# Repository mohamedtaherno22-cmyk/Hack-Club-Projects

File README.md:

Super Starbie
Super Starbie is a small, interactive desktop pet. Its a Starbie but with customized to my liking.

## What Can Super Starbie Do?

- **Weather Updates:** Check the weather, temperature, and humidity.
- **Time and Date:** Keep track of the current time and date, add timers and reminders.
- **Have Expressions:** Display simple expressions that give it its own character.
- **Have motion-based interactions.**.
- **Utilize AI in some sort:** Haven't decided yet how to do this; I'll do it in the build week.

## Feautres

- **5 Mechanical Switches:** The project has multiple buttons placed around the PCB, making it easy to interact with the device and trigger different functions.

- **ESP32 Microcontroller:** The ESP32 acts as the brain of the project, handling the inputs, controlling the display, and providing wireless connectivity.

- **OLED Display:** The built-in display can show useful information, icons, and simple animations, making the device more interactive and easier to use.

- **Motion Sensing: ** The MPU6050 sensor detects movement and changes in orientation, allowing the device to react to physical movement.

- **Temperature and Humidity Sensor:** DHT11 measures the surrounding temperature and humidity, allowing the device to display them.

## PCB & Components

## 3D Image

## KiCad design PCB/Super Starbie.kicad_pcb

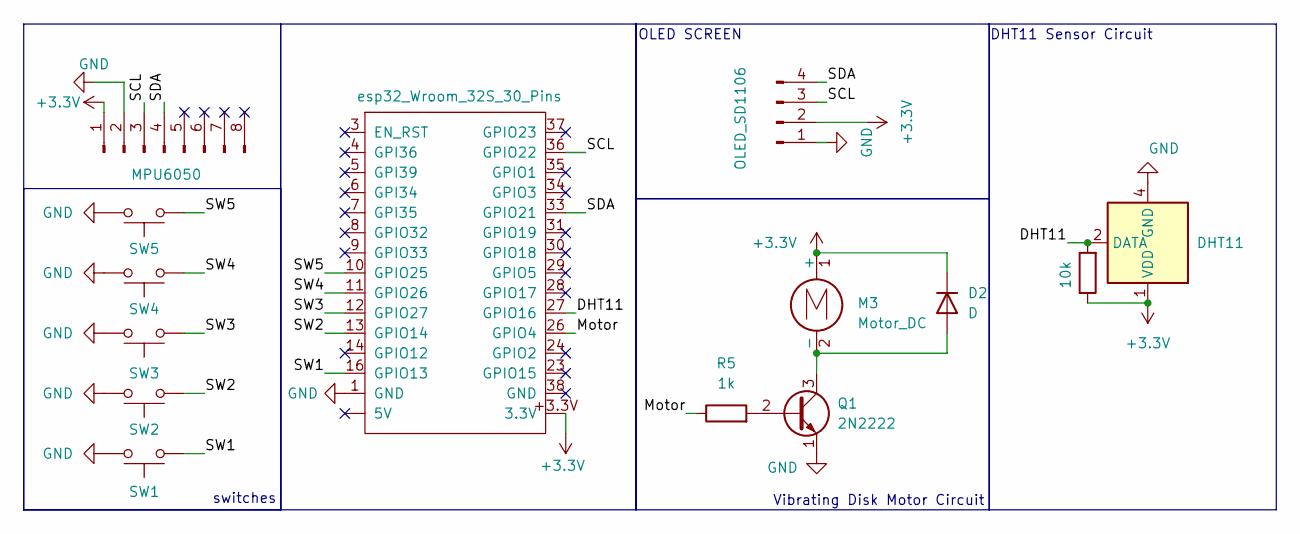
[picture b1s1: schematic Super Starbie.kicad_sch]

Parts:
D2: D; D_DO-35_SOD27_P7.62mm_Horizontal
J4: MPU6050; PinHeader_1x08_P2.54mm_Vertical
J5: OLED_SD1106; Display_128x64_096_I2C
M3: Motor_DC; PinHeader_1x02_P2.54mm_Vertical
Q1: 2N2222; TO-92_Inline_Wide
R1: 10k; R_Axial_DIN0204_L3.6mm_D1.6mm_P7.62mm_Horizontal
R5: 1k; R_Axial_DIN0204_L3.6mm_D1.6mm_P7.62mm_Horizontal
SW1, SW2, SW3, SW4, SW5: SW_Push; SW_Cherry_MX_1.00u_PCB
U3: esp32_Wroom_32S_30_Pins; THE NEW FOOTPRINTER
U4: DHT11; Aosong_DHT11_5.5x12.0_P2.54mm

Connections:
+3.3V: D2.1 (K), J4.1, J5.2, M3.1 (+), R1.1, U3.+3.3V (3.3V), U4.1 (VDD)
/DHT11: R1.2, U3.27 (GPIO16), U4.2 (DATA)
/Motor: R5.1, U3.26 (GPIO4)
/SCL: J4.3, J5.3, U3.36 (GPIO22)
/SDA: J4.4, J5.4, U3.33 (GPIO21)
/SW1: SW1.1, U3.16 (GPIO13)
/SW2: SW2.1, U3.13 (GPIO14)
/SW3: SW3.1, U3.12 (GPIO27)
/SW4: SW4.1, U3.11 (GPIO26)
/SW5: SW5.1, U3.10 (GPIO25)
GND: J4.2, J5.1, Q1.1 (E), SW1.2, SW2.2, SW3.2, SW4.2, SW5.2, U3.1 (GND), U4.4 (GND)
unnamed: D2.2 (A), M3.2 (-), Q1.3 (C)
unnamed: Q1.2 (B), R5.2

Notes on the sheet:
switches
DHT11 Sensor Circuit
OLED SCREEN
Vibrating Disk Motor Circuit

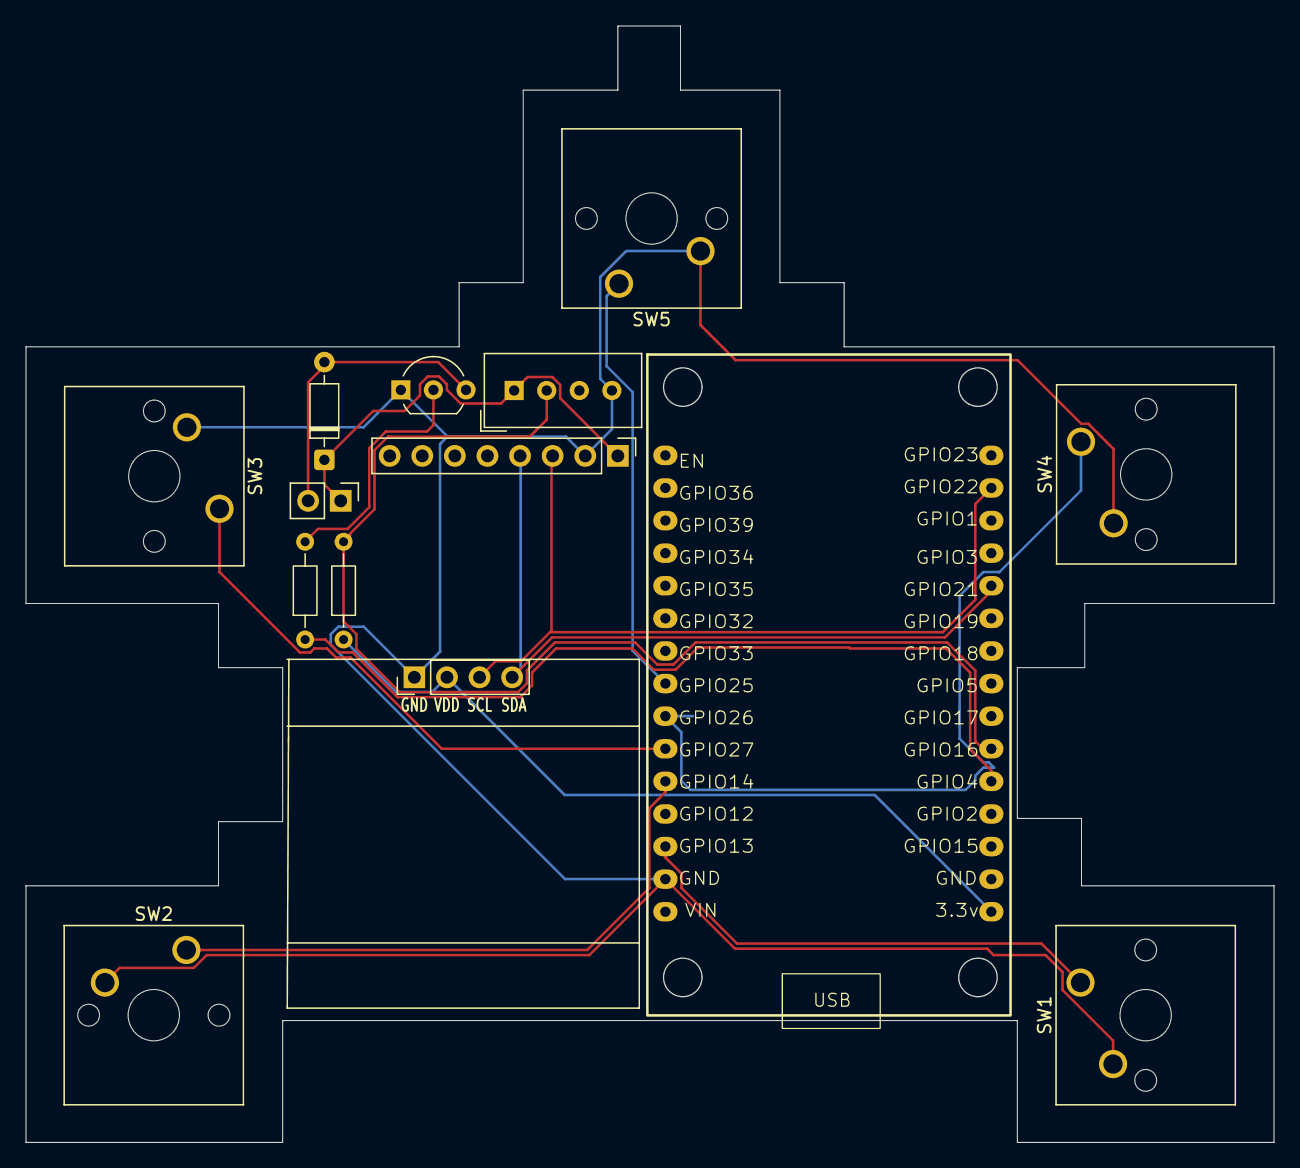
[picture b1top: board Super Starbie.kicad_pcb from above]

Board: 2 copper layers, 97.2 x 87.0 mm, 14 parts (0 on the bottom side), 13 nets.
